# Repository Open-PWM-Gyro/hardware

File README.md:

# Open-PWM-Gyro Hardware

This repository is a collection of hardware designs (KiCad projects) that can be used with the Open-PWM-Gyro firmware and software.

Each design lives in its own folder, and each folder name matches the board target name used in the firmware repository.

- Firmware: https://github.com/Open-PWM-Gyro/firmware
- Config app: **WIP**

## Designs

| Folder | Description | Status |
| --- | --- | --- |
| [`xiao-stm32c5/`](xiao-stm32c5/) | Seeed Studio XIAO STM32C5 module on a simple carrier board, designed to be easy to build by hand | Released |
| [`custom-stm32c5/`](custom-stm32c5/) | Fully custom board built around an STM32C5 | Planned |
| [`legacy/custom-stm32g4/`](legacy/custom-stm32g4/) | Original custom board built around an STM32G4 | Retired |

## Retired: custom-stm32g4

The STM32G431 design has been retired and is kept only for reference. It is not recommended for new builds, for two reasons:

- The STM32G431 has become much more expensive than the STM32C5.
- The status LED draws the absolute maximum rated current of an MCU IO pin.

The STM32C5 designs above replace it.

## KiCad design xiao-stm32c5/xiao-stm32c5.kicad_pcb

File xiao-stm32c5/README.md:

# Description
Carrier board for a `SeeedStudio XIAO STM32C5` that allows it to be used as a 7-channel gyro for RC planes

# Features
- Only 8 total components (including the `XIAO STM32C5`)
  - 3 are truly needed (22uF servo bulk capacitor, XIAO V<sub>in</sub> diode, servo pin header)
  - JST connector (J1) is optional and only needed if you intend on connecting a receiver to it
- Bi-color indicator LED (blue, red)
- Hand-solder-friendly components/footprints
- 3 possible serial receiver connections
  1. Receiver serial output connected to pin header DIN/CH7
  2. Receiver UART soldered to solder pads
  3. Receiver UART connected to JST connector
- Channel 7 is dual-purpose (can either be a serial receiver input, or a channel output)
  - It's also a separate UART so it can be used as a PWM output if the receiver is connected to the solder pads or the JST connector

# Layer Stackup
This is a 4-layer board with the following stackup:

1. Signal + Power
2. Ground
3. Ground
4. Signal

Both ground layers are solid ground pours and aren't shown in the images section below

# BOM
Reference|Qty|Value|MPN
---|---|---|---
C1|1|22u|EEE-FK1H220P
D1|1|LED_Dual_AKAK|150141RB73100
D2|1|D_Schottky|SD1206S040S1R0
J1|1|Conn_01x04_MountingPin|SM04B-SRSS-TB
J2|1|Conn_03x07|TSW-107-26-F-T
R1|1|150|RC0805FR-07150RL
R2|1|33|RC0805FR-0733RL
U1|1|XIAO-STM32C5-SMD|

> [!NOTE]
> J2 is a 3x7 2.54mm pitch pin header. This part can be replaced with three 7-pin headers or seven 3-pin headers or some other combination to save cost

# Usage
WIP

# Images
## Schematic

## PCB
### Top Layer

### Bottom Layer

### Top + Bottom Layer

## 3D View
### Top

### Bottom

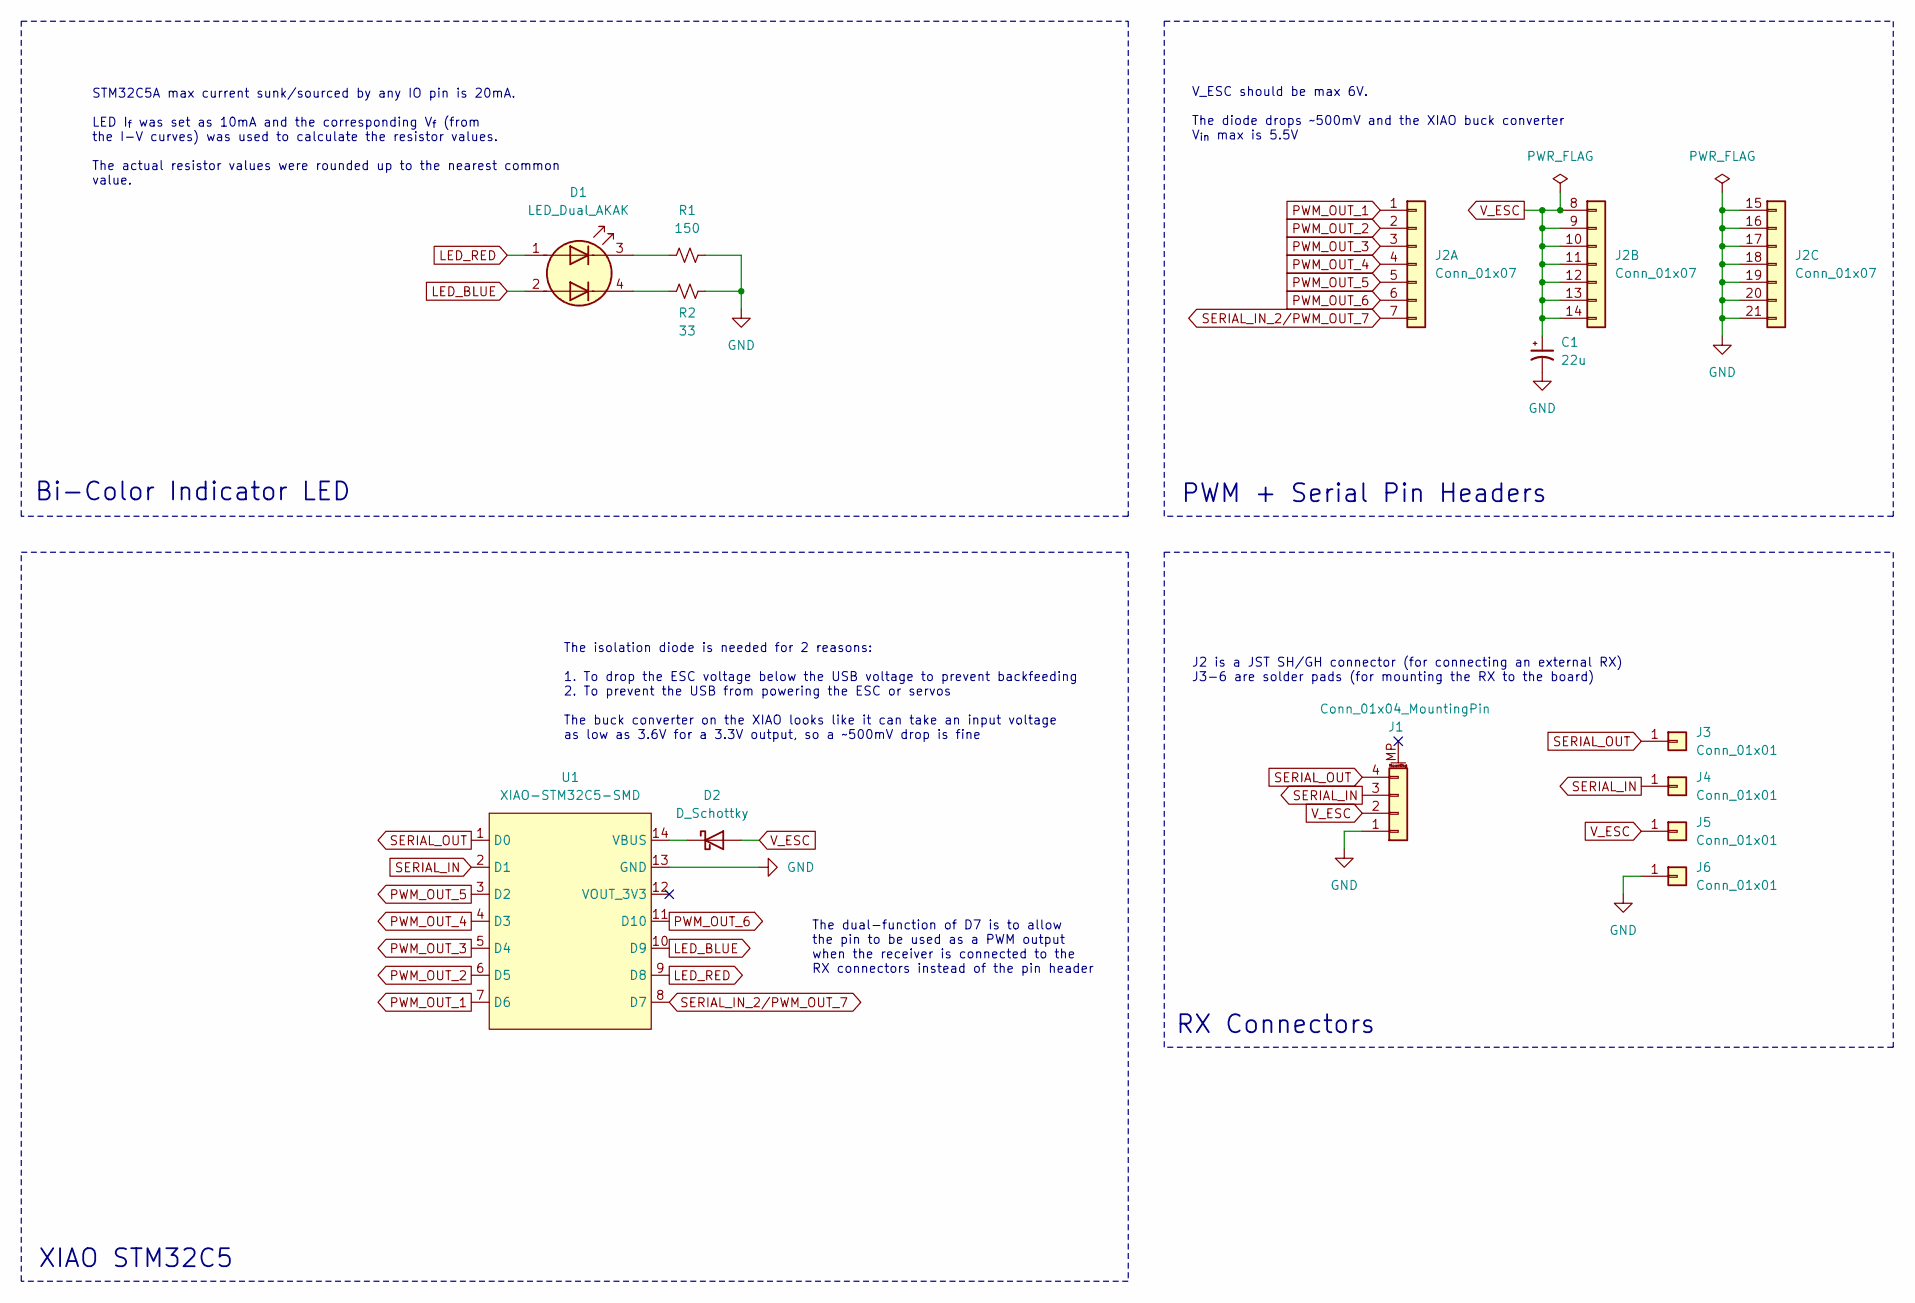
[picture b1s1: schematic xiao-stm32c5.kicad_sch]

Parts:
C1: 22u; CP_Elec_4x5.4; MPN EEE-FK1H220P
D1: LED_Dual_AKAK; WL-SBTW_3528; MPN 150141RB73100
D2: D_Schottky; D_1206_3216Metric_Pad1.42x1.75mm_HandSolder; MPN SD1206S040S1R0
J1: Conn_01x04_MountingPin; JST_SH_SM04B-SRSS-TB_1x04-1MP_P1.00mm_Horizontal; MPN SM04B-SRSS-TB
J2: Conn_01x07; PinHeader_3x07_P2.54mm_Vertical; MPN TSW-107-26-F-T
J3, J4, J5, J6: Conn_01x01; SolderWirePad_1x01_SMD_2x4mm
R1: 150; R_0805_2012Metric_Pad1.20x1.40mm_HandSolder; MPN RC0805FR-07150RL
R2: 33; R_0805_2012Metric_Pad1.20x1.40mm_HandSolder; MPN RC0805FR-0733RL
U1: XIAO-STM32C5-SMD; XIAO-STM32C5-SMD-Simple

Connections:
GND: C1.2, J1.1, J2.15, J2.16, J2.17, J2.18, J2.19, J2.20, J2.21, J6.1 (Pin_1_1), R1.2, R2.2, U1.13 (GND)
LED_BLUE: D1.2 (A2), U1.10 (D9)
LED_RED: D1.1 (A1), U1.9 (D8)
unnamed: D1.3 (K1), R1.1
unnamed: D1.4 (K2), R2.1
unnamed: D2.1 (K), U1.14 (VBUS)
PWM_OUT_1: J2.1, U1.7 (D6)
PWM_OUT_2: J2.2, U1.6 (D5)
PWM_OUT_3: J2.3, U1.5 (D4)
PWM_OUT_4: J2.4, U1.4 (D3)
PWM_OUT_5: J2.5, U1.3 (D2)
PWM_OUT_6: J2.6, U1.11 (D10)
SERIAL_IN: J1.3, J4.1 (Pin_1_1), U1.2 (D1)
SERIAL_IN_2/PWM_OUT_7: J2.7, U1.8 (D7)
SERIAL_OUT: J1.4, J3.1 (Pin_1_1), U1.1 (D0)
V_ESC: C1.1, D2.2 (A), J1.2, J2.8, J2.9, J2.10, J2.11, J2.12, J2.13, J2.14, J5.1 (Pin_1_1)

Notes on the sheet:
STM32C5A max current sunk/sourced by any IO pin is 20mA. LED I_{f} was set as 10mA and the corresponding V_{f} (from the I-V curves) was used to calculate the resistor values. The actual resistor values were rounded up to the nearest common value.
XIAO STM32C5
J2 is a JST SH/GH connector (for connecting an external RX) J3-6 are solder pads (for mounting the RX to the board)
The isolation diode is needed for 2 reasons: 1. To drop the ESC voltage below the USB voltage to prevent backfeeding 2. To prevent the USB from powering the ESC or servos The buck converter on the XIAO looks like it can take an input voltage as low as 3.6V for a 3.3V output, so a ~500mV drop is fine
Bi-Color Indicator LED
V_ESC should be max 6V. The diode drops ~500mV and the XIAO buck converter V_{in} max is 5.5V
PWM + Serial Pin Headers
RX Connectors
The dual-function of D7 is to allow the pin to be used as a PWM output when the receiver is connected to the RX connectors instead of the pin header

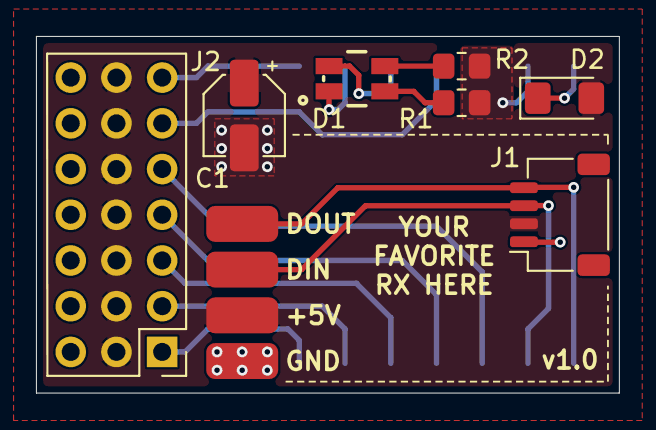
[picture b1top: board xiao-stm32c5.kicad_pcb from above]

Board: 4 copper layers, 32.4 x 19.8 mm, 12 parts (1 on the bottom side), 16 nets.
